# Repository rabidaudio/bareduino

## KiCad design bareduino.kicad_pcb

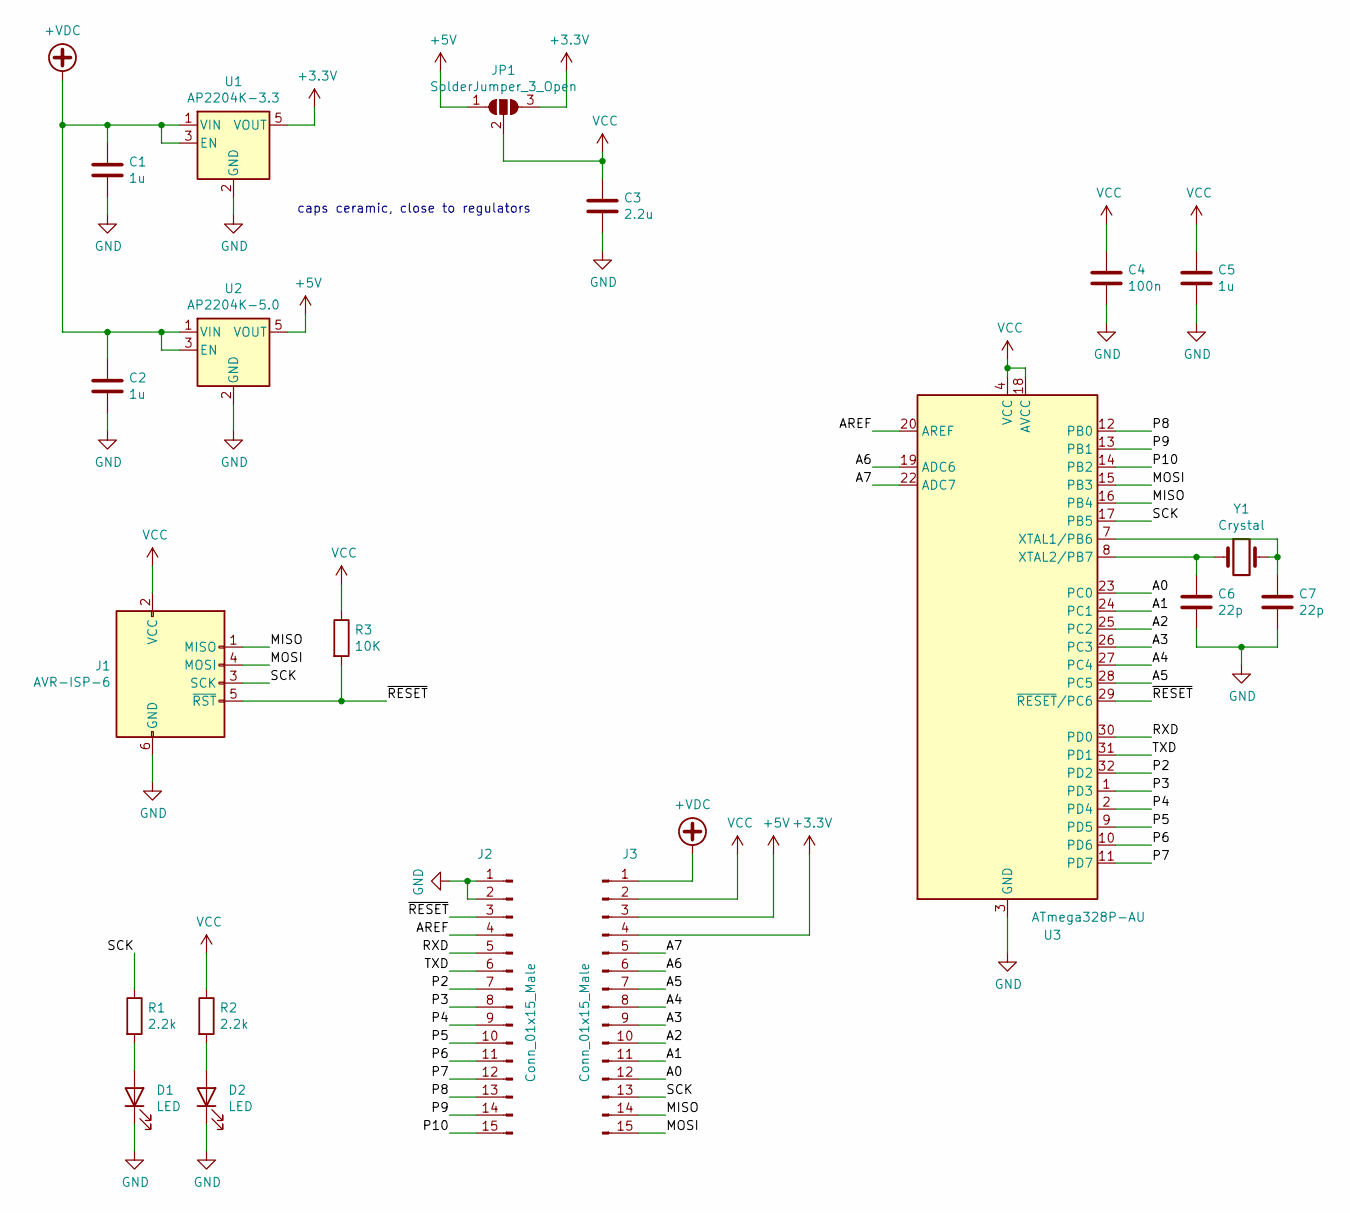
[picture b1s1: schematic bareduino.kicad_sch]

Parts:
C1, C2, C5: 1u; C_0603_1608Metric
C3: 2.2u; C_0603_1608Metric
C4: 100n; C_0603_1608Metric
C6, C7: 22p; C_0603_1608Metric
D1, D2: LED; LED_0603_1608Metric
J1: AVR-ISP-6; PinHeader_2x03_P2.54mm_Vertical
J2, J3: Conn_01x15_Male; PinHeader_1x15_P2.54mm_Vertical
JP1: SolderJumper_3_Open; SolderJumper-3_P1.3mm_Open_RoundedPad1.0x1.5mm
R1, R2: 2.2k; R_0603_1608Metric
R3: 10K; R_0603_1608Metric
U1: AP2204K-3.3; SOT-23-5
U2: AP2204K-5.0; SOT-23-5
U3: ATmega328P-AU; TQFP-32_7x7mm_P0.8mm
Y1: Crystal; Crystal_HC49-U_Vertical

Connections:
+3V3: J3.4, JP1.3 (B), U1.5 (VOUT)
+5V: J3.3, JP1.1 (A), U2.5 (VOUT)
+VDC: C1.1, C2.1, J3.1, U1.1 (VIN), U1.3 (EN), U2.1 (VIN), U2.3 (EN)
/A0: J3.12, U3.23 (PC0)
/A1: J3.11, U3.24 (PC1)
/A2: J3.10, U3.25 (PC2)
/A3: J3.9, U3.26 (PC3)
/A4: J3.8, U3.27 (PC4)
/A5: J3.7, U3.28 (PC5)
/A6: J3.6, U3.19 (ADC6)
/A7: J3.5, U3.22 (ADC7)
/AREF: J2.4, U3.20 (AREF)
/MISO: J1.1 (MISO), J3.14, U3.16 (PB4)
/MOSI: J1.4 (MOSI), J3.15, U3.15 (PB3)
/P2: J2.7, U3.32 (PD2)
/P3: J2.8, U3.1 (PD3)
/P4: J2.9, U3.2 (PD4)
/P5: J2.10, U3.9 (PD5)
/P6: J2.11, U3.10 (PD6)
/P7: J2.12, U3.11 (PD7)
/P8: J2.13, U3.12 (PB0)
/P9: J2.14, U3.13 (PB1)
/P10: J2.15, U3.14 (PB2)
/RXD: J2.5, U3.30 (PD0)
/SCK: J1.3 (SCK), J3.13, R1.1, U3.17 (PB5)
/TXD: J2.6, U3.31 (PD1)
/~RESET: J1.5 (~RST), J2.3, R3.2, U3.29 (~RESET/PC6)
GND: C1.2, C2.2, C3.2, C4.2, C5.2, C6.2, C7.2, D1.1 (K), D2.1 (K), J1.6 (GND), J2.1, J2.2, U1.2 (GND), U2.2 (GND), U3.3 (GND), U3.5 (GND), U3.21 (GND)
unnamed: C6.1, U3.8 (XTAL2/PB7), Y1.1
unnamed: C7.1, U3.7 (XTAL1/PB6), Y1.2
unnamed: D1.2 (A), R1.2
unnamed: D2.2 (A), R2.2
VCC: C3.1, C4.1, C5.1, J1.2 (VCC), J3.2, JP1.2 (C), R2.1, R3.1, U3.4 (VCC), U3.6 (VCC), U3.18 (AVCC)

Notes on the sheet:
caps ceramic, close to regulators

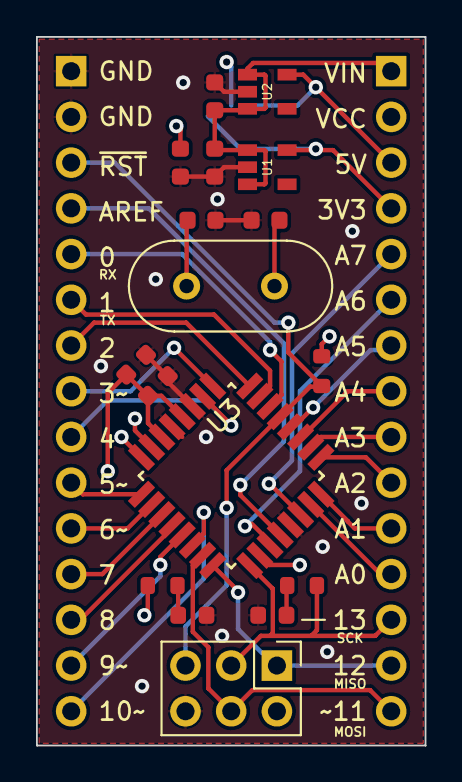
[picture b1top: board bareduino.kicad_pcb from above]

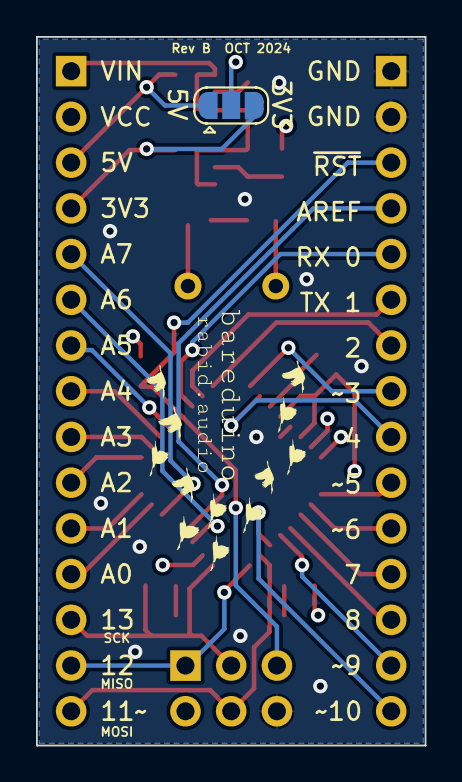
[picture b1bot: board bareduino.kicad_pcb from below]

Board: 4 copper layers, 21.6 x 39.4 mm, 20 parts (3 on the bottom side), 33 nets.

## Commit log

2024-10-12 revision B
2024-10-12 graphics and gerbers
